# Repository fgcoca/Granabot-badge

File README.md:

# **Documentación del badge Granabot** 
Se trata de una PCB diseñada en base al logo de Granabot como un kit de soldadura SMD y se basa en un micro controlador ATTiny85 y unos cuantos LEDs con control inteligente tipo WS2812B.

![GrB][1]

 [1]: https://github.com/fgcoca/Granabot-badge/blob/master/Images/Top-Botton.png

# **Contenidos del repositorio**
1. Diseños originales de Gustavo Reynaga de la PCB realizados con [KICad](http://kicad.org/)

    * [Granabot badge original](https://github.com/fgcoca/Granabot-badge/tree/master/Granabot-Badge-Original)
    * [Imágenes para el diseño](https://github.com/fgcoca/Granabot-badge/tree/master/Granabot-Badge-Original/Design/images)
    * [Diseño para el patrocinio de PCBWay](https://github.com/fgcoca/Granabot-badge/tree/master/Granabot-Badge-Original/Hardware/PCBWay)
    * [Diseño para patrocinio de OSH Park](https://github.com/fgcoca/Granabot-badge/tree/master/Granabot-Badge-Original/Hardware/OSHPark)
2. Debido a dos pequeños errores de encapsulado en el diseño original de Gustavo se hace necesaria la revisión de este para dotar al Attiny85 y al diodo MBRA140 de footprint correctos. La citada revisión y adaptación la Realiza francisco López.

    * [Granabot badge revisado](https://github.com/fgcoca/Granabot-badge/tree/master/Granabot-Badge-revisado)
    * [Diseño para el patrocinio de PCBWay](https://github.com/fgcoca/Granabot-badge/tree/master/Granabot-Badge-revisado/Hardware/PCBWay)
    * [Diseño para patrocinio de OSH Park](https://github.com/fgcoca/Granabot-badge/tree/master/Granabot-Badge-revisado/Hardware/OSHPark)
   
3. Firmware de prueba cargado en los badges que se entregan que sirve para probar el funcionamiento simplemente con alimentarlo. Se trata de un archivo .ino listo para cargarr en el ATTiny85 via ICSP. En el [manual de uso](https://github.com/fgcoca/Granabot-badge/blob/master/Kit/Programacion/Manual.pdf) se explican todos los detalles para trabajar con el badge.
    * [Firmware](https://github.com/fgcoca/Granabot-badge/tree/master/Firmware/badge_granabot)

4. El Kit. Al badge Granabot se le da formato de kit para su entrega estando este formado por la PCB, los componentes necesarios para montarlo, un manual de montaje impreso y una fe de erratas. Todo ello introducido en una cajita adornada con [pegatinas](https://github.com/fgcoca/Granabot-badge/tree/master/Pegatinas-Caja) de Granabot y de los patrocinadores. En las imágenes se ve el aspecto final del kit listo para su entrega de una caja individual y de un conjunto de cajas preparadas para su entrega el día de la celebración del evento [Granabot](https://sites.google.com/site/granabot18/)

![Vista desde la derecha][10] ![Conjunto visto desde la izquierda][11]

 [10]: https://github.com/fgcoca/Granabot-badge/blob/master/Images/VDcha.jpg
 [11]: https://github.com/fgcoca/Granabot-badge/blob/master/Images/VIzdaConj.jpg

En la imagen vemos a Juan Robles de [Createc](https://createc3d.com/) (uno de nuestros patrocinadores) con el badge recien entregado.

![Juan Robles][12]

 [12]: https://github.com/fgcoca/Granabot-badge/blob/master/Images/Juan.jpg

5. Información del kit Granabot

    * [Listas de materiales](https://github.com/fgcoca/Granabot-badge/tree/master/Kit/BOM)
      * [Formato .odt](https://github.com/fgcoca/Granabot-badge/blob/master/Kit/BOM/BOM-con-links-compras.ods)
      * [Formato .pdf](https://github.com/fgcoca/Granabot-badge/blob/master/Kit/BOM/BOM-con-links-compras.pdf)
      * [Formato .png](https://github.com/fgcoca/Granabot-badge/blob/master/Kit/BOM/BOM.png)      
    * [Erratas en la primera edición del kit](https://github.com/fgcoca/Granabot-badge/tree/master/Kit/Erratas)
      * [Formato .odt](https://github.com/fgcoca/Granabot-badge/blob/master/Kit/Erratas/Erratas.odt)
      * [Formato .pdf](https://github.com/fgcoca/Granabot-badge/blob/master/Kit/Erratas/Erratas.pdf)      
    * [Manuales de montaje](https://github.com/fgcoca/Granabot-badge/tree/master/Kit/Montaje)
      * [Formato comprimido .7z](https://github.com/fgcoca/Granabot-badge/blob/master/Kit/Montaje/Manual-montaje.7z)
      * [Formato .pdf](https://github.com/fgcoca/Granabot-badge/blob/master/Kit/Montaje/Manual-montaje.pdf)
      * [Formato .png](https://github.com/fgcoca/Granabot-badge/blob/master/Kit/Montaje/Manual-montaje.png)      
    * [Manuales de configuraciones y uso de librerias para programar el kit](https://github.com/fgcoca/Granabot-badge/tree/master/Kit/Programacion)
      * [Formato .odt](https://github.com/fgcoca/Granabot-badge/blob/master/Kit/Programacion/Manual.odt)
      * [Formato .pdf](https://github.com/fgcoca/Granabot-badge/blob/master/Kit/Programacion/Manual.pdf)
      * [Video de funcionamiento](https://github.com/fgcoca/Granabot-badge/blob/master/Kit/Programacion/video/Test-badge-Granabot.mp4)       
    * [Programando físicamente el kit](https://github.com/fgcoca/Granabot-badge/tree/master/Kit/Programando)
      * [Formato .odt](https://github.com/fgcoca/Granabot-badge/blob/master/Kit/Programando/Programando.odt)
      * [Formato .pdf](https://github.com/fgcoca/Granabot-badge/blob/master/Kit/Programando/Programando.pdf)        
    * [Pinza de sujeción diseñada en 3D](https://github.com/fgcoca/Granabot-badge/tree/master/Kit/Programando/Design)
      * [Diseño en FreeCAD](https://github.com/fgcoca/Granabot-badge/blob/master/Kit/Programando/Design/Pinzas-Centrador.FCStd)
      * [Archivo stl de la pinza](https://github.com/fgcoca/Granabot-badge/blob/master/Kit/Programando/Design/Pinza.stl)  
      * [Archivo stl de la pieza usada para posicionar el chip](https://github.com/fgcoca/Granabot-badge/blob/master/Kit/Programando/Design/Centrador.stl)

![Guía de posicionado][20] ![Pinza de sujeción con el muelle montado][21]

 [20]: https://github.com/fgcoca/Granabot-badge/blob/master/Kit/Programando/Images/03Guia-posicionadoM.jpg
 [21]: https://github.com/fgcoca/Granabot-badge/blob/master/Kit/Programando/Images/10Pinza-sujecionM.jpg

# **Enlaces**

[Web de Granabot 2018](https://sites.google.com/site/granabot18/)

# **Autores**
Gustavo Reynaga https://github.com/hulkco @gsreynaga 

Jorge Pérez https://github.com/akirasan @akirasan

José Antonio Vacas https://github.com/javacasm @javacasm

Federico Coca Caba https://github.com/fgcoca @fgcoca

Francisco López Castro @flopcas 

# **Licencia**
![License][88]

 [88]: https://github.com/fgcoca/3D-Design_Robots_Other/blob/master/Lapicero/Licencia/licencia.png
[Enlace al texto de la licencia](https://github.com/fgcoca/Granabot-badge/blob/master/LICENSE)

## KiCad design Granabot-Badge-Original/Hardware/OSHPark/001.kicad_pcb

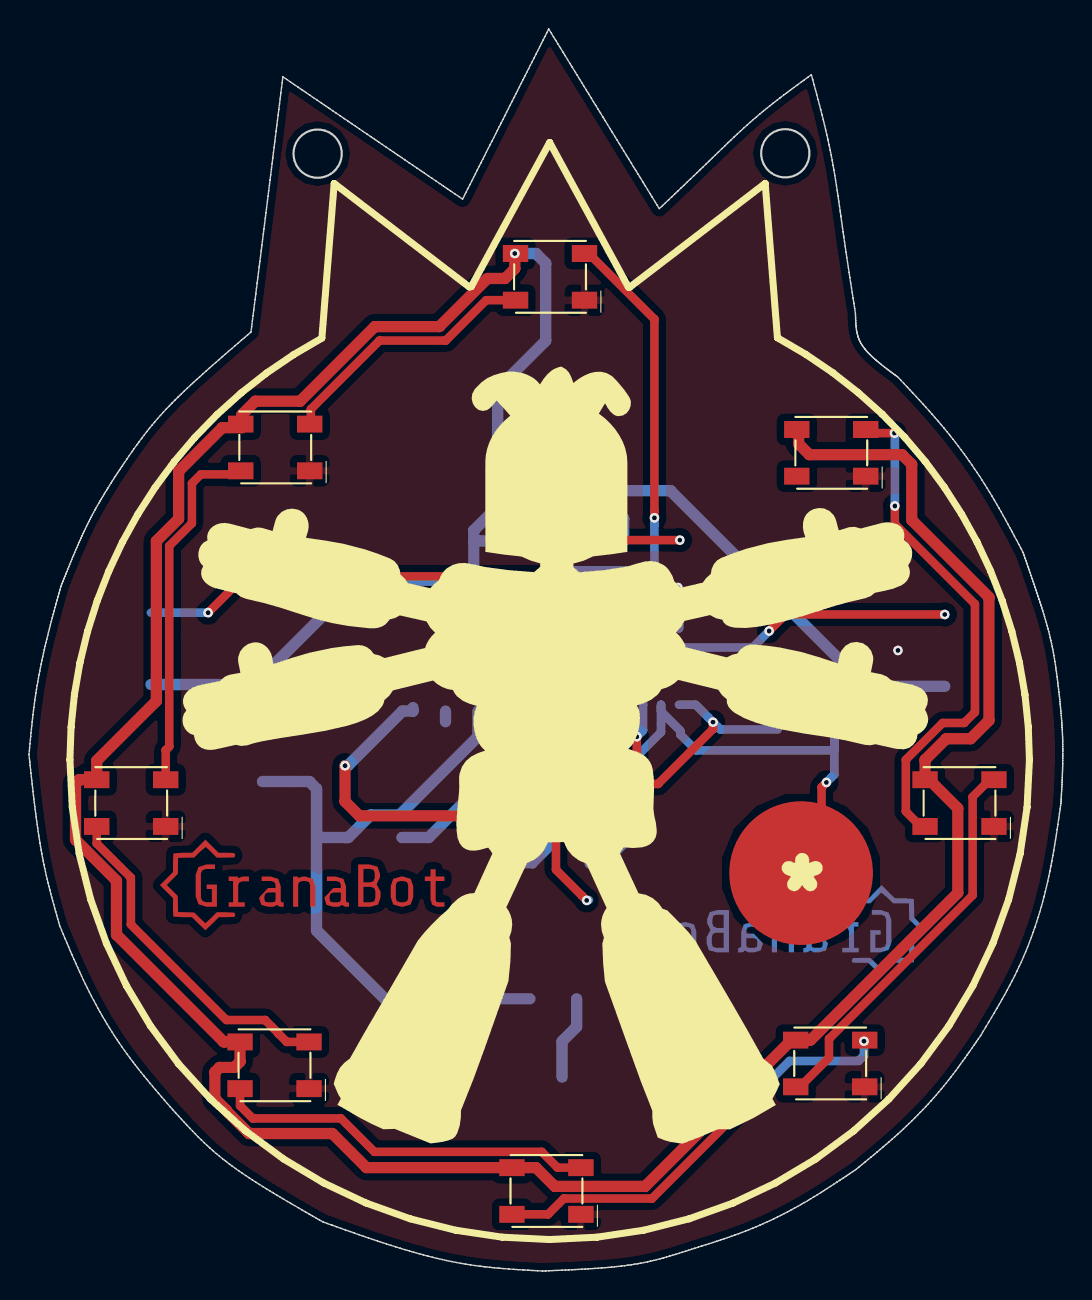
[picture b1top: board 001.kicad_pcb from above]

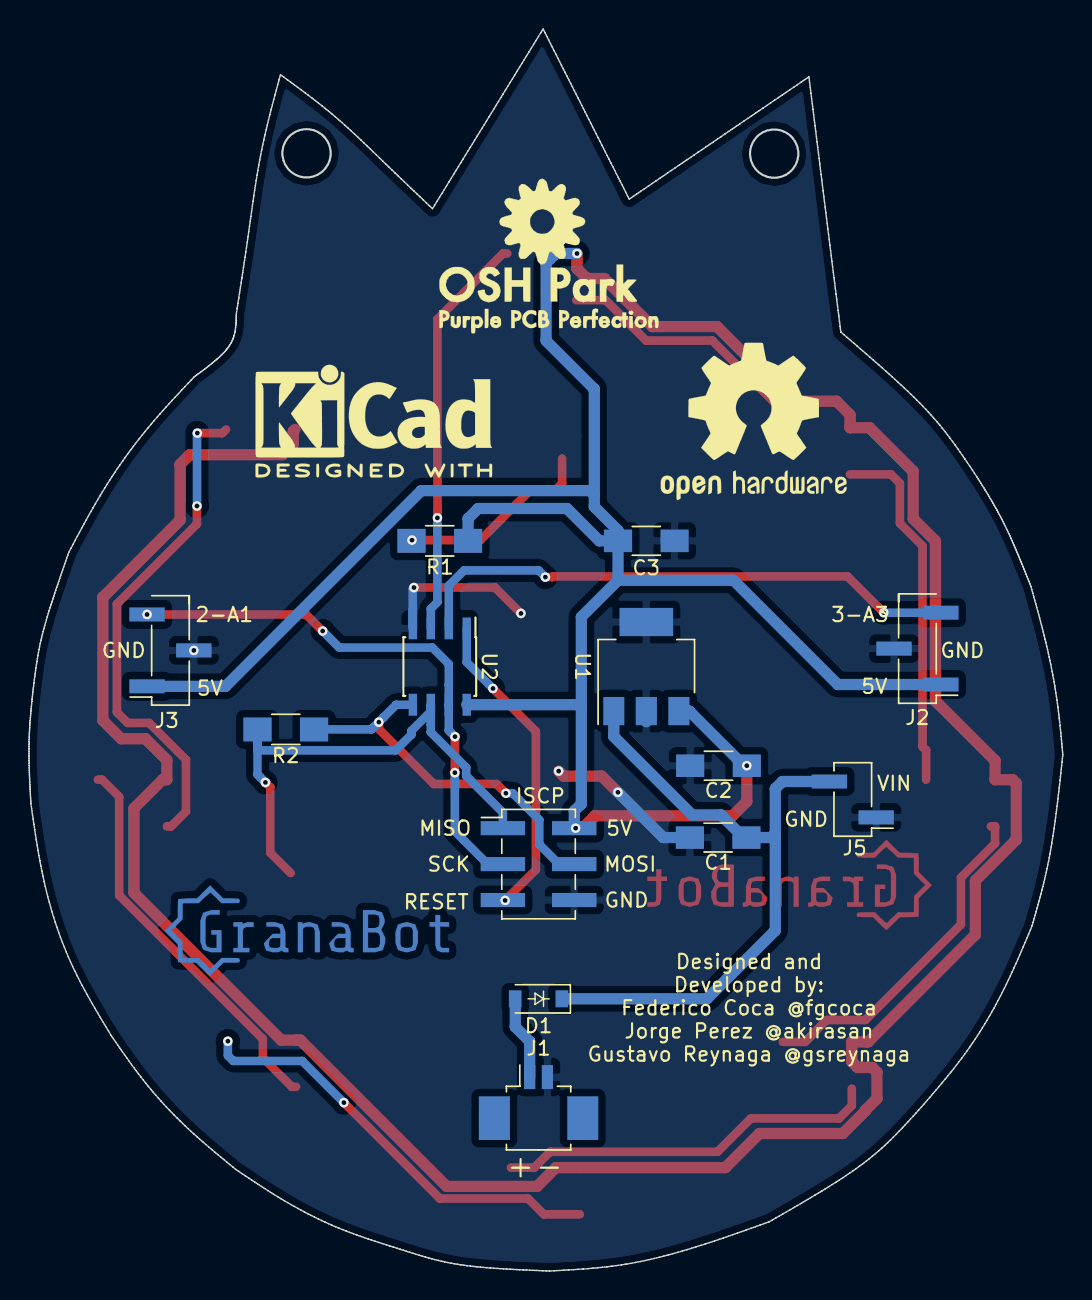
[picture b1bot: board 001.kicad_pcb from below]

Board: 2 copper layers, 73.1 x 87.8 mm, 28 parts (15 on the bottom side), 18 nets.

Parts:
C1: 0.22uF; C_1206_HandSoldering
C2: 0.1uF; C_1206_HandSoldering
C3: 22nF; C_1206_HandSoldering
CAP1: CAPSENSE_CIRCLE; CAPSENSE-CIRCLE2-D10MM
D1: MBRA140; D_SOD-123
D2: ON; LED_1206_HandSoldering
J1: CONN_01X02; Molex_PicoBlade_53261-0271_02x1.25mm_Angled
J2: CONN_01X03; Pin_Header_Straight_1x03_Pitch2.54mm_SMD_Pin1Left
J3: CONN_01X03; Pin_Header_Straight_1x03_Pitch2.54mm_SMD_Pin1Right
J4: CONN_02X03; Pin_Header_Straight_2x03_Pitch2.54mm_SMD
J5: CONN_01X02; Pin_Header_Straight_1x02_Pitch2.54mm_SMD_Pin1Left
LED1, LED2, LED3, LED4, LED5, LED6, LED7, LED8: WS2812B
R1: 1k; R_1206_HandSoldering
R2: 1M Ohms; R_1206_HandSoldering
U1: LM340MP-5.0/NOPB; SOT-223-3Lead_TabPin2
U2: ATTINY85-20SU; SOIC-8_3.9x4.9mm_Pitch1.27mm
svg2mod1: G***1; logo_letra_Cu
svg2mod2: G***2; logo_letra_Mask
svg2mod3: G***3; logo_letra_Cu
svg2mod4: G***4; logo_letra_Mask
svg2mod4#2: G***4; hormiga con borde

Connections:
3-A3: J2.3, U2.2
4-A2: LED1.2, U2.3
+5V: C2.1, C3.1, J2.1, J3.1, J4.2, LED1.3, LED2.3, LED3.3, LED4.3, LED5.3, LED6.3, LED7.3, LED8.3, R1.1, U1.3, U2.8
GND: C1.2, C2.2, C3.2, D2.1, J1.2, J2.2, J3.2, J4.6, J5.1, LED1.1, LED2.1, LED3.1, LED4.1, LED5.1, LED6.1, LED7.1, LED8.1, U1.2, U2.4
MISO-1-PWM: CAP1.1, J4.1, R2.2, U2.6
MOSI-0-PWM: J4.4, R2.1, U2.5
unnamed: D2.2, R1.2
unnamed: LED1.4, LED2.2
unnamed: LED2.4, LED3.2
unnamed: LED3.4, LED4.2
unnamed: LED4.4, LED5.2
unnamed: LED5.4, LED6.2
unnamed: LED6.4, LED7.2
unnamed: LED7.4, LED8.2
RESET: J4.5, U2.1
SCK-2-A1: J3.3, J4.3, U2.7
VBAT: D1.2, J1.1
VCC: C1.1, D1.1, J5.2, U1.1

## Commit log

2021-11-09 Update README.md
    https://forum.kicad.info/t/warning-avoid-all-links-to-kicad-pcb-org-use-kicad-org/31521
